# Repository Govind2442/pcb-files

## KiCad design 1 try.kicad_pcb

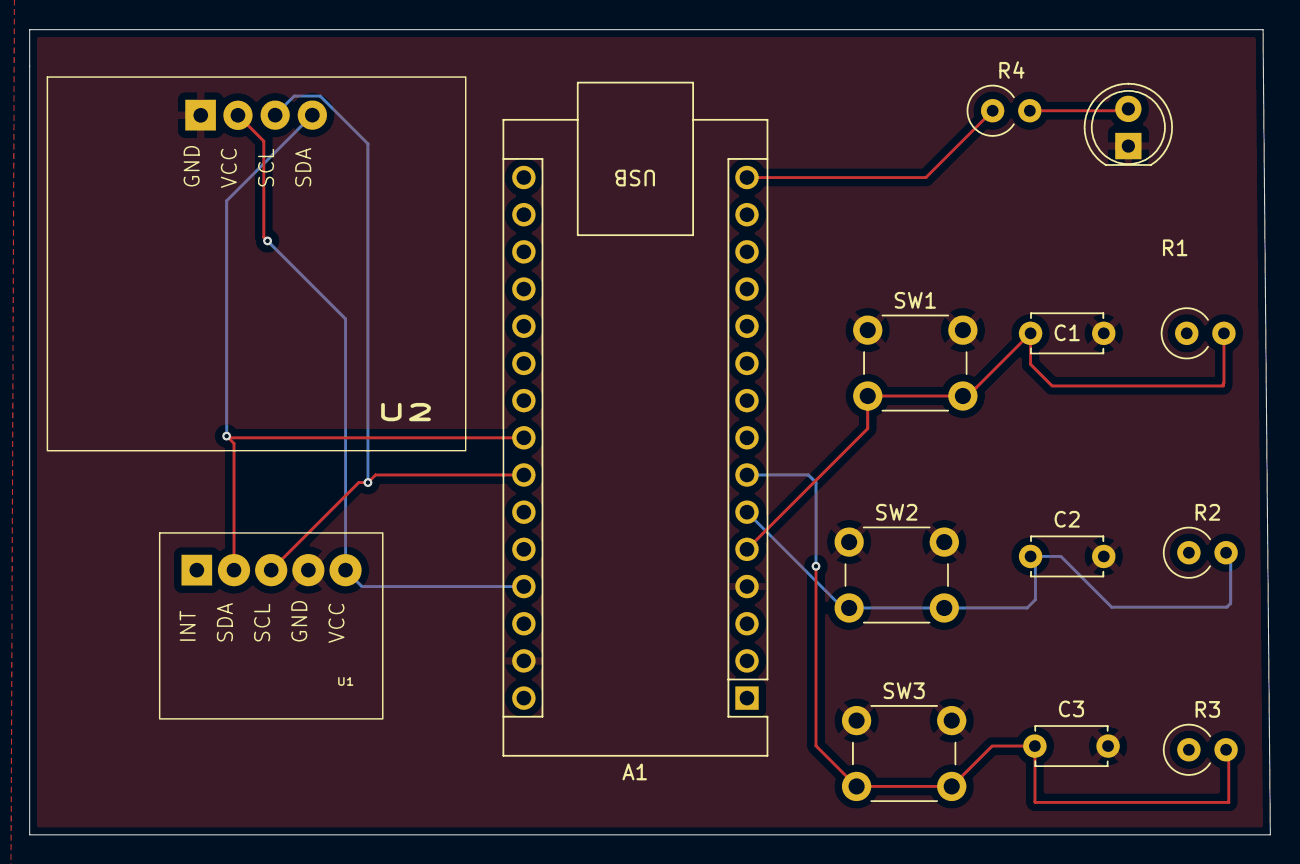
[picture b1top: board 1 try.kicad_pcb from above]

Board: 2 copper layers, 84.8 x 55.0 mm, 14 parts (0 on the bottom side), 9 nets.

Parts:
A1: Arduino_Nano_v3.x; Arduino_Nano
C1, C2, C3: 100n; C_Disc_D4.7mm_W2.5mm_P5.00mm
PCB-1: LED; LED_D5.0mm
R1, R2, R3, R4: 1k; R_Axial_DIN0309_L9.0mm_D3.2mm_P2.54mm_Vertical
SW1, SW2, SW3: SW_Push; SW_PUSH_6mm_H4.3mm
U1: Max30102_5 pin inp
U2: ssd1306

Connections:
+5V: A1.27 (+5V), R1.1, R2.1, R3.1, U1.5 (VCC), U2.2
GND: A1.4 (GND), A1.29 (GND), C1.2, C2.2, C3.2, PCB-1.1 (K), SW1.1, SW2.1, SW3.1, U1.4 (GND), U2.1
unnamed: A1.23 (A4), U1.2 (SDA), U2.4 (gnd)
unnamed: A1.24 (A5), U1.3 (SCL), U2.3 (vcc)
unnamed: A1.5 (D2), C1.1, R1.2, SW1.2
unnamed: A1.6 (D3), C2.1, R2.2, SW2.2
unnamed: A1.7 (D4), C3.1, R3.2, SW3.2
unnamed: A1.15 (D12), R4.1
unnamed: PCB-1.2 (A), R4.2
